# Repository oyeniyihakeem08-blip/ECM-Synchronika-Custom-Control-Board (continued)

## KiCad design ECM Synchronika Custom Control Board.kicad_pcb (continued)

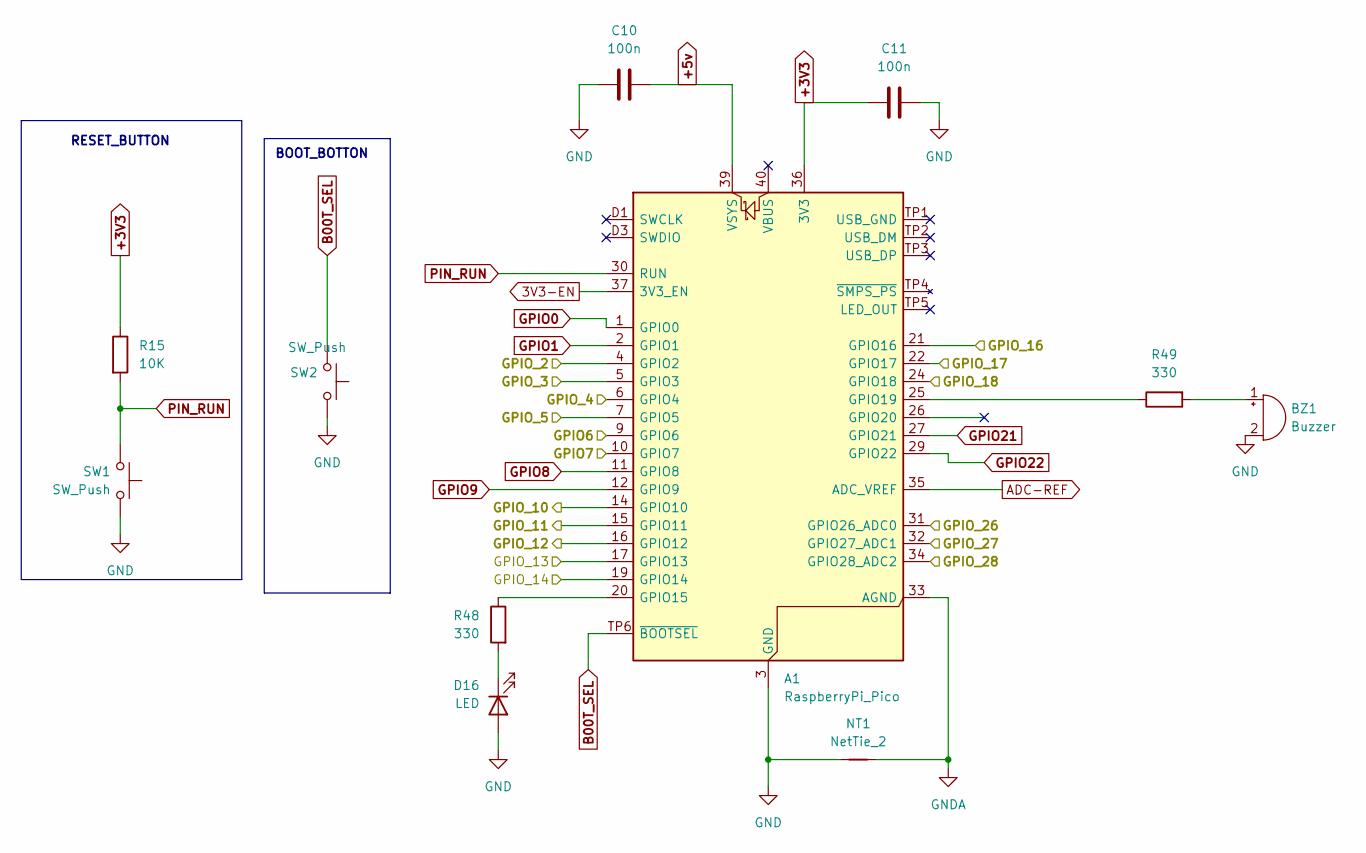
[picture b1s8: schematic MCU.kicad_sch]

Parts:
A1: RaspberryPi_Pico; RaspberryPi_Pico_SMD
BZ1: Buzzer; Buzzer_12x9.5RM7.6
C10, C11: 100n; C_0603_1608Metric
D16: LED; LED_0805_2012Metric
NT1: NetTie_2; NetTie-2_SMD_Pad2.0mm
R15: 10K; R_0603_1608Metric
R48, R49: 330; R_0805_2012Metric
SW1, SW2: SW_Push; SW_PUSH_6mm

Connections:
3V3-EN: A1.37 (3V3_EN); also elsewhere on the board
+3V3: A1.36 (3V3), C11.1, R15.1; also elsewhere on the board
+5v: A1.39 (VSYS), C10.2; also elsewhere on the board
/MCU (page 4)/GPIO6: A1.9 (GPIO6); also elsewhere on the board
/MCU (page 4)/GPIO7: A1.10 (GPIO7); also elsewhere on the board
/MCU (page 4)/GPIO_2: A1.4 (GPIO2); also elsewhere on the board
/MCU (page 4)/GPIO_3: A1.5 (GPIO3); also elsewhere on the board
/MCU (page 4)/GPIO_4: A1.6 (GPIO4); also elsewhere on the board
/MCU (page 4)/GPIO_5: A1.7 (GPIO5); also elsewhere on the board
/MCU (page 4)/GPIO_10: A1.14 (GPIO10); also elsewhere on the board
/MCU (page 4)/GPIO_11: A1.15 (GPIO11); also elsewhere on the board
/MCU (page 4)/GPIO_12: A1.16 (GPIO12); also elsewhere on the board
/MCU (page 4)/GPIO_13: A1.17 (GPIO13); also elsewhere on the board
/MCU (page 4)/GPIO_14: A1.19 (GPIO14); also elsewhere on the board
/MCU (page 4)/GPIO_16: A1.21 (GPIO16); also elsewhere on the board
/MCU (page 4)/GPIO_17: A1.22 (GPIO17); also elsewhere on the board
/MCU (page 4)/GPIO_18: A1.24 (GPIO18); also elsewhere on the board
/MCU (page 4)/GPIO_26: A1.31 (GPIO26_ADC0); also elsewhere on the board
/MCU (page 4)/GPIO_27: A1.32 (GPIO27_ADC1); also elsewhere on the board
/SENSOR INPUT/GPIO_28: A1.34 (GPIO28_ADC2); also elsewhere on the board
ADC-REF: A1.35 (ADC_VREF); also elsewhere on the board
B00T_SEL: A1.TP6 (~BOOTSEL), SW2.2; also elsewhere on the board
GND: A1.3 (GND), A1.8 (GND), A1.13 (GND), A1.18 (GND), A1.23 (GND), A1.28 (GND), A1.38 (GND), A1.D2 (GND), BZ1.2 (-), C10.1, C11.2, D16.2 (A), NT1.1, SW1.1, SW2.1; also elsewhere on the board
GNDA: A1.33 (AGND), NT1.2; also elsewhere on the board
GPIO0: A1.1 (GPIO0); also elsewhere on the board
GPIO1: A1.2 (GPIO1); also elsewhere on the board
GPIO8: A1.11 (GPIO8); also elsewhere on the board
GPIO9: A1.12 (GPIO9); also elsewhere on the board
GPIO21: A1.27 (GPIO21); also elsewhere on the board
GPIO22: A1.29 (GPIO22); also elsewhere on the board
unnamed: A1.20 (GPIO15), R48.1
unnamed: A1.25 (GPIO19), R49.1
unnamed: BZ1.1 (+), R49.2
unnamed: D16.1 (K), R48.2
PIN_RUN: A1.30 (RUN), R15.2, SW1.2; also elsewhere on the board

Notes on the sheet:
RESET_BUTTON
BOOT_BOTTON

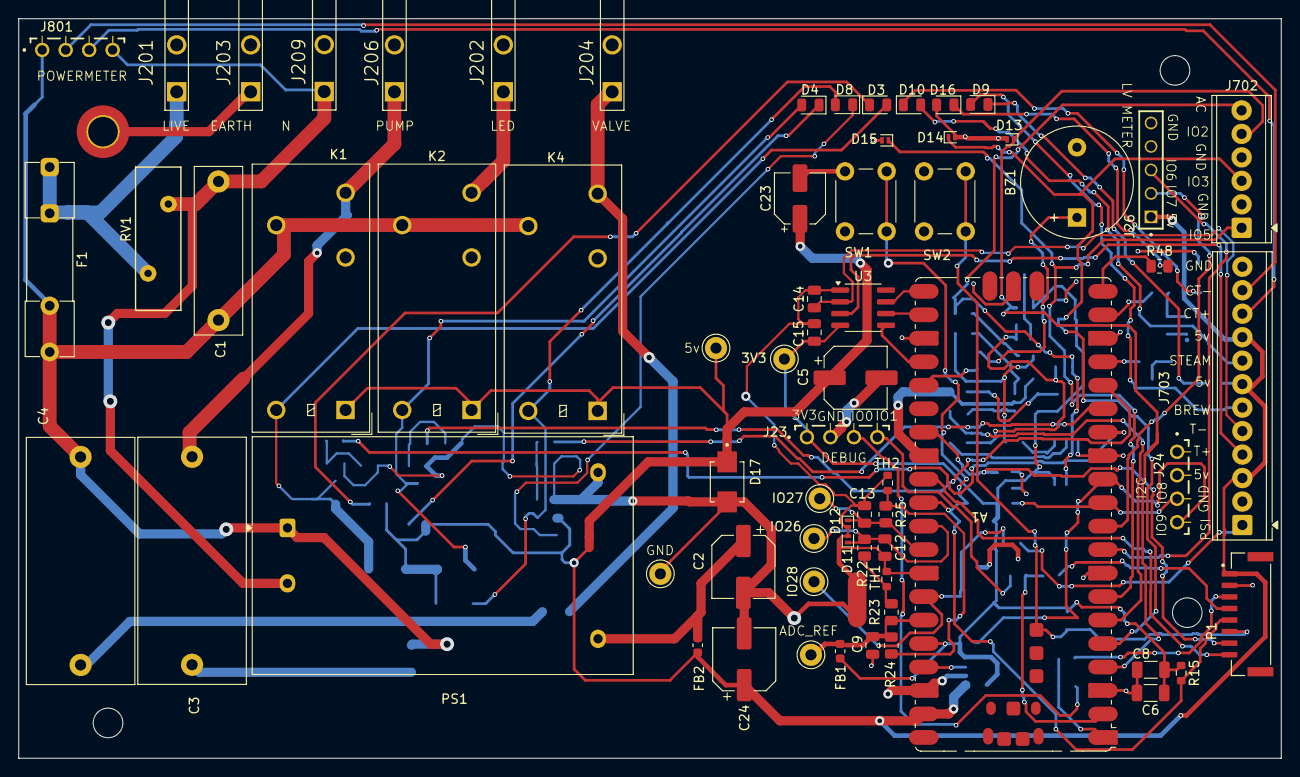
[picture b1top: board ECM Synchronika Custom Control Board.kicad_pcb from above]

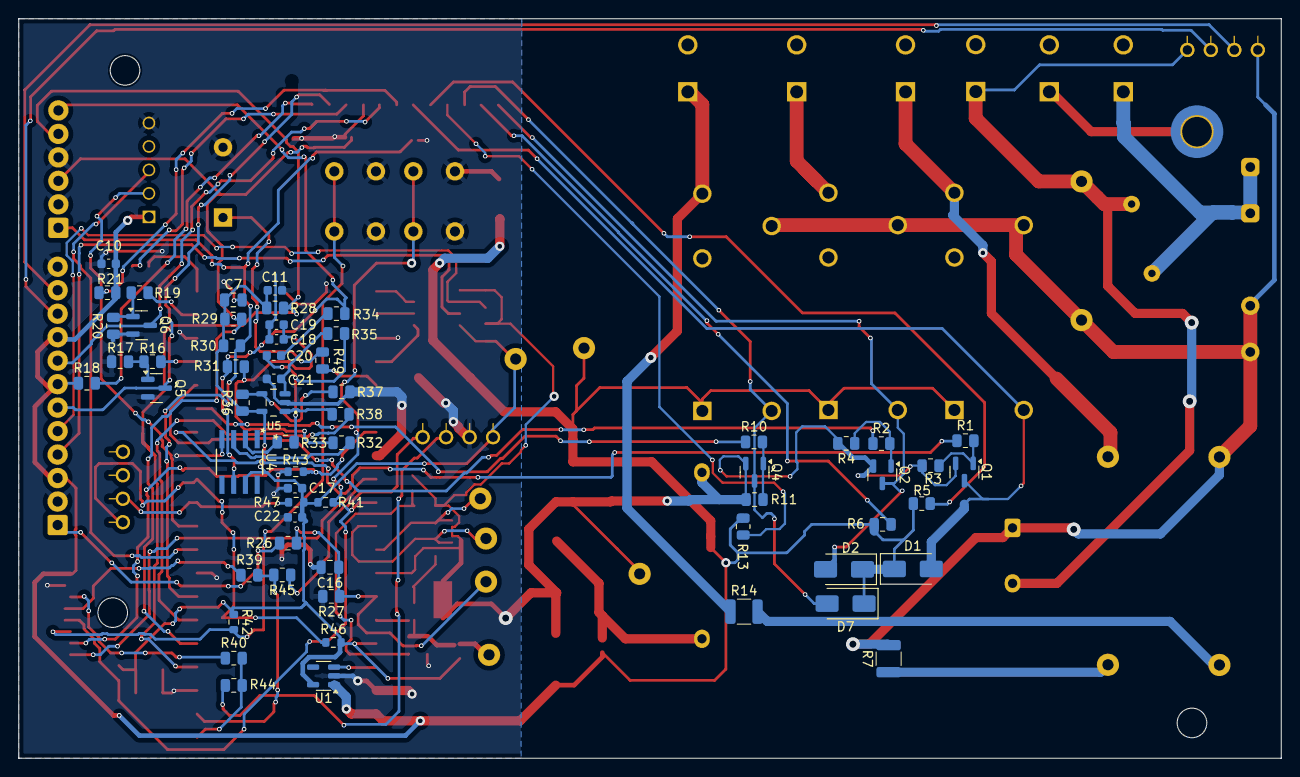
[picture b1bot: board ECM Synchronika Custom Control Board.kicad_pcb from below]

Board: 2 copper layers, 136.6 x 80.0 mm, 133 parts (61 on the bottom side), 80 nets.

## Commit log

2025-11-29 init project
2025-11-29 New updated
2025-11-29 SCHEMATIC CONTINUATION
2025-11-29 Update KiCad project files
2025-12-03 Deleted Spare relays
2025-12-05 Updated PCB files
